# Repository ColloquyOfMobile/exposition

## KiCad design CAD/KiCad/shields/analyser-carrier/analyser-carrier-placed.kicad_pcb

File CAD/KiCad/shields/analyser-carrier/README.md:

# Direct-plug DFRobot analyser carrier

A second [continuous-wire schematic](wired/README.md) is available in `wired/`,
with an editable KiCad schematic and PDF. It preserves the original circuit,
uses no electrical net labels, and documents the drawing changes and the
purpose/necessity of existing test points and module modifications.

Five modified DFR0126 Audio Analyzer V2.0 modules plug directly into this
150 x 55mm carrier. Each site has one gold 1x6 female socket and one gold
1x2 female socket, both 2.54mm pitch. Downward male headers on the modules
mate with them; no module-to-carrier cables are used. The carrier's keyed
JA1 connector and two retention holes still match the backplane.

**Unmodified modules must not be plugged in.** The microphone feeds the
module's L input. The output is brought to the R-input header by the
following conversion. The user chose L for the microphone on 2026-10-19;
until then the conversion was the mirror image (R4 removed, L to OUT,
microphone on R). The white output connector can remain fitted but is unused.

The 2026-10-19 carrier revision follows this assignment at all five sites:
contact 1 = `microphone` (L), contact 4 = `analyser out` (converted R).
Schematic, copper, silkscreen, mechanical notes and fabrication packages
use the same mapping. Older carrier artwork requires the earlier module
conversion; do not mix revisions. Physical socket fit still needs checking.

## Convert each module

1. With power disconnected, remove **module R3, the 22K right-input summing
   resistor**. This is on the DFRobot module, not the carrier. If reference
   markings differ, identify the resistor between R and the input summing
   node from the schematic/continuity before removing it. Leave R4 (left
   input, the microphone's path) and the MSGEQ7 clock/reference parts in place.
2. Link the now-isolated **R signal terminal to OUT**, using a short insulated
   jumper on the module's component side. OUT is MSGEQ7 pin 3 and the signal
   contact of the white output connector. Do not connect it to +5V or GND.
   R3 must be removed first; otherwise this feeds output back into the input.
3. Refit the input connector positions as a downward-facing 1x6 male header
   (or two aligned 1x3 headers) and the control connector as a downward-facing
   1x2 male header. All eight mating pins point toward the carrier. Mark R as
   OUT permanently. The R input is no longer available for audio.
4. Before power, check continuity OUT-to-converted-R, continuity from L to
   R4, supply polarity at the mating pins, and isolation of converted R from
   the removed R3 summing-side pad. Check there is no solder bridge between
   +5V and ground. Confirm with the meter that the header pin reaching R4 sits
   at contact 1 and the one reaching R3 at contact 4: the L-then-R order of
   the two groups is photo-derived (below).
5. Seat the module fully in both sockets, then select nylon standoffs/shims
   matching that seated PCB gap. Do not force a predetermined spacer height
   against the sockets. M3 hardware retains the module; it does not pull the
   connectors into alignment. Module 0 is rotated 180 degrees.

DFRobot's V2 schematic identifies R4 as the left branch, R3 as the right,
and U1.3 as OUT:
https://dfimg.dfrobot.com/wiki/17648/DFR0126_msgeq7-spectrum-analyzer-module_schematics_V1.pdf
Both branches are 22K into one node, then C4 (0.01 uF) into MSGEQ7 IN, so
L and R are electrically interchangeable: the choice only decides which
header pin carries the microphone.

## Socket mapping

The table describes the carrier component-side view in each module's local
coordinate frame. The round mounting hole is (0,0); the slot is (20.32,0).
Module 0 rotates this complete pattern 180 degrees; the others do not.
Coordinates are **photo-derived assumptions**, not a manufacturer land pattern.

| Contact | Local X mm | Local Y mm | Signal / module marking |
|---|---:|---:|---|
| 1 | 3.81 | -5.08 | L microphone input |
| 2 | 6.35 | -5.08 | +5V (left group) |
| 3 | 8.89 | -5.08 | GND (left group) |
| 4 | 11.43 | -5.08 | OUT, formerly R |
| 5 | 13.97 | -5.08 | +5V (right group) |
| 6 | 16.51 | -5.08 | GND (right group) |
| 7 | 16.51 | 17.78 | R reset |
| 8 | 19.05 | 17.78 | S strobe |

All module +5V contacts use MEGA_5V; all module grounds use AGND. No digital
GND bond is added. The microphone signal feeds the L input. This table
matches the current schematic and copper.
ANA0-4, AGND and MEGA5V probe pads remain accessible. Leave the carrier out
when the Teensy adapter is fitted.

On 2026-10-08 the two-pin socket on each module position moved 1.27 mm
in local -X to match the corrected DFRobot J4. Reset now aligns in X with
input contact 6. Attached tracks and the nearby reset escape bends were
adjusted; native DRC reports zero violations and zero unconnected items.

## Photo-derived fit

The user authorized using the supplied photographs and standard pitch on
2026-10-07. The adopted grid has 2.54mm pin pitch and 22.86mm row separation.
Header offsets relative to holes, group ordering/orientation and the 20.32mm
hole spacing are inferred and require a physical fit/polarity check. The
29 x 32mm module envelope is also estimated. A 3.2mm hole and 5.74 x 3.2mm
slot allow mounting adjustment, but **slots do not correct socket misalignment**.

Print mounting-template.svg at 100%, verify its 50mm scale, then compare all
eight module pins and both mounting holes. Confirm against one converted
module before manufacturing the set. This is an engineering prototype, not
a fit-verified fabrication release. Native DRC does not prove connector fit.
mechanical.json preserves these assumptions; socket-assembly.csv lists hardware.

M1-M5 in the KiCad BOM are composite module/socket assemblies. Fit the purchased
modules after soldering sockets to the carrier; do not solder the modules to it.
Use carrier.py to regenerate, then route.py, finish.py, planes.py, check.py and
verify.py. The latter independently checks all eight mating pad positions/nets.

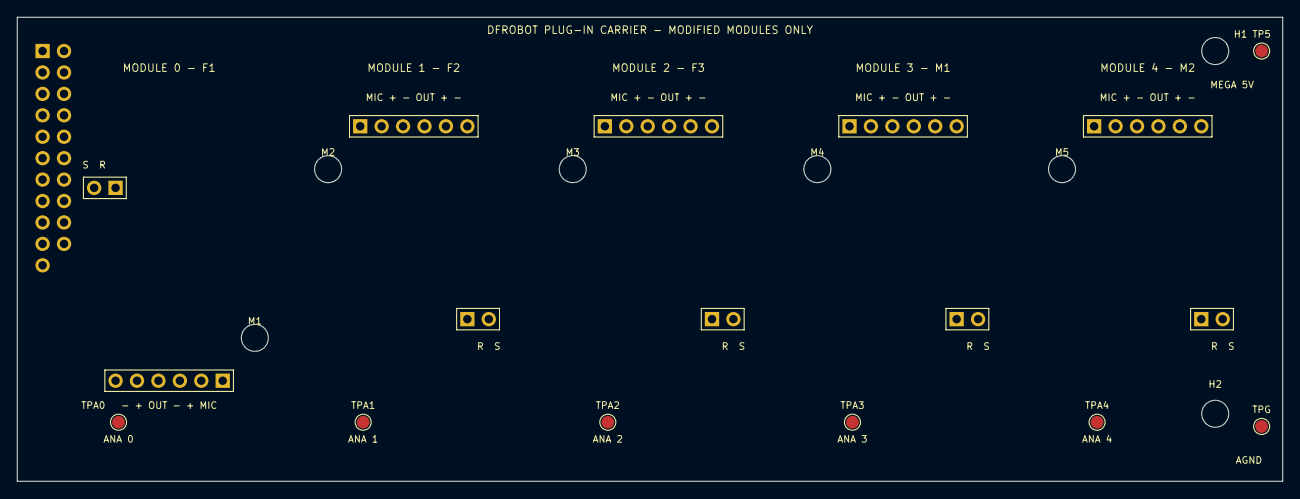
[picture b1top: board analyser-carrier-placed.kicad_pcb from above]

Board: 2 copper layers, 150.0 x 55.0 mm, 15 parts (1 on the bottom side), 14 nets, no tracks yet.

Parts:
H1, H2: M3 carrier retention; MountingHole_3.2mm_M3
JA1: ANALYSER - KEY 22; Socket_2x11_Key22_PlugCarrier
M1, M2, M3, M4, M5: DFR0126 MODIFIED / PLUG-IN; DFR0126_PlugIn_Photo
TP5: MEGA_5V; TestPoint_Pad_D1.5mm
TPA0: female1/analyser out; TestPoint_Pad_D1.5mm
TPA1: female2/analyser out; TestPoint_Pad_D1.5mm
TPA2: female3/analyser out; TestPoint_Pad_D1.5mm
TPA3: male1/analyser out; TestPoint_Pad_D1.5mm
TPA4: male2/analyser out; TestPoint_Pad_D1.5mm
TPG: AGND; TestPoint_Pad_D1.5mm

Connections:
AGND: JA1.2, JA1.4, JA1.6, JA1.8, JA1.10, JA1.16, M1.3, M1.6, M2.3, M2.6, M3.3, M3.6, M4.3, M4.6, M5.3, M5.6, TPG.1
MEGA_5V: JA1.19, M1.2, M1.5, M2.2, M2.5, M3.2, M3.5, M4.2, M4.5, M5.2, M5.5, TP5.1
analyser/reset: JA1.18, M1.7, M2.7, M3.7, M4.7, M5.7
analyser/strobe: JA1.17, M1.8, M2.8, M3.8, M4.8, M5.8
female1/analyser out: JA1.11, M1.4, TPA0.1
female1/microphone: JA1.1, M1.1
female2/analyser out: JA1.12, M2.4, TPA1.1
female2/microphone: JA1.3, M2.1
female3/analyser out: JA1.13, M3.4, TPA2.1
female3/microphone: JA1.5, M3.1
male1/analyser out: JA1.14, M4.4, TPA3.1
male1/microphone: JA1.7, M4.1
male2/analyser out: JA1.15, M5.4, TPA4.1
male2/microphone: JA1.9, M5.1

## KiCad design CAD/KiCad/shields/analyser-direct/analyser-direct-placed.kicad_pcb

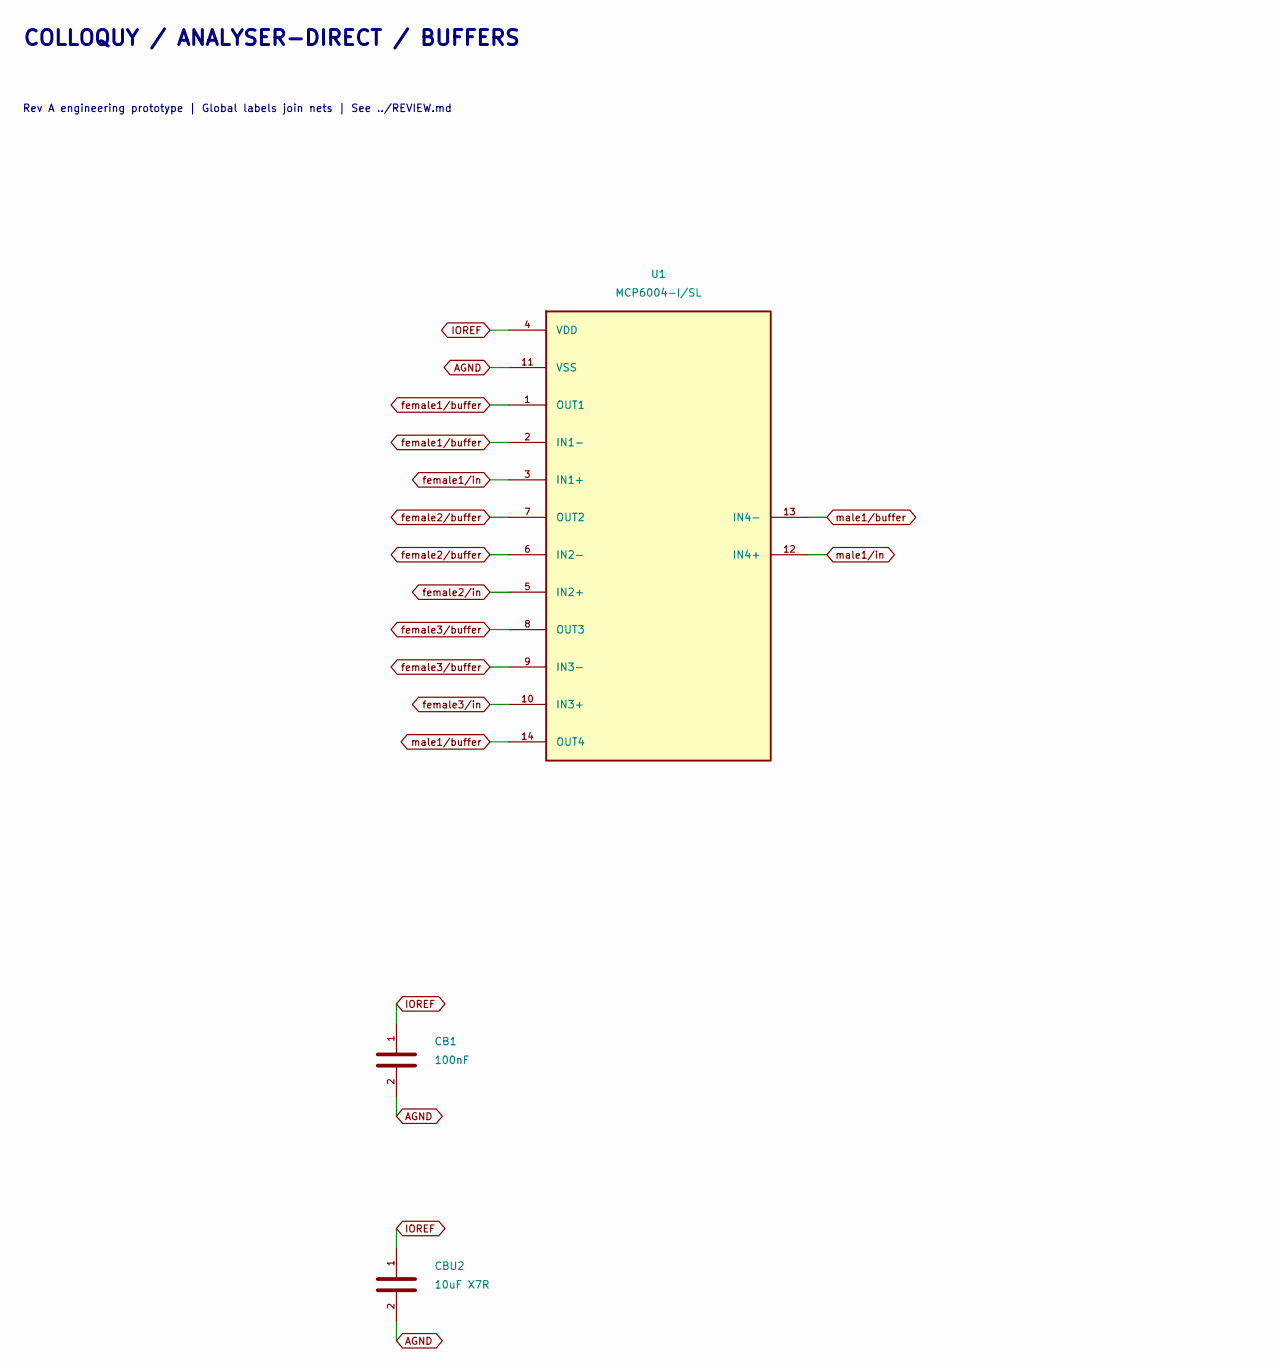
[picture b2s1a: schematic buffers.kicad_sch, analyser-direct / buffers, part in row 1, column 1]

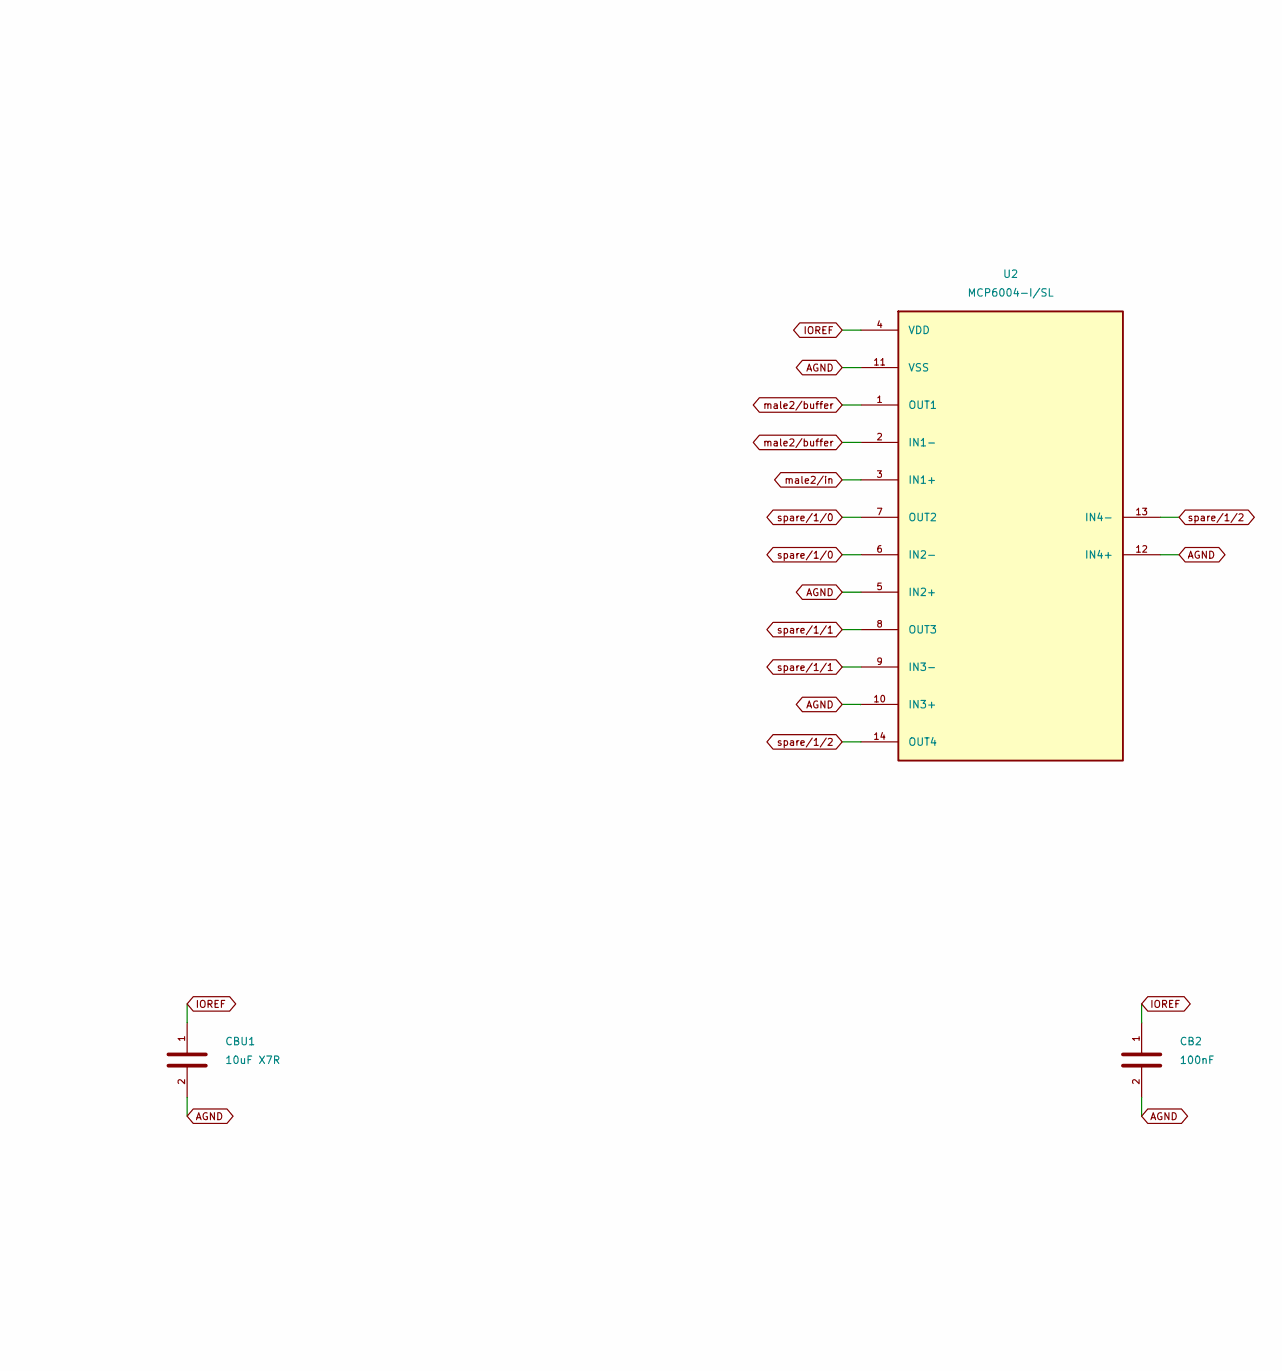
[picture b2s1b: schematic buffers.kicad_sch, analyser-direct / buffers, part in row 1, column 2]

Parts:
CB1, CB2: 100nF; C_0603_1608Metric
CBU1, CBU2: 10uF X7R; C_0805_2012Metric
U1, U2: MCP6004-I/SL; SOIC-14_3.9x8.7mm_P1.27mm

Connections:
AGND: CB1.2, CB2.2, CBU1.2, CBU2.2, U1.11 (VSS), U2.5 (IN2+), U2.10 (IN3+), U2.11 (VSS), U2.12 (IN4+); also elsewhere on the board
IOREF: CB1.1, CB2.1, CBU1.1, CBU2.1, U1.4 (VDD), U2.4 (VDD); also elsewhere on the board
female1/buffer: U1.1 (OUT1), U1.2 (IN1-); also elsewhere on the board
female1/in: U1.3 (IN1+); also elsewhere on the board
female2/buffer: U1.6 (IN2-), U1.7 (OUT2); also elsewhere on the board
female2/in: U1.5 (IN2+); also elsewhere on the board
female3/buffer: U1.8 (OUT3), U1.9 (IN3-); also elsewhere on the board
female3/in: U1.10 (IN3+); also elsewhere on the board
male1/buffer: U1.13 (IN4-), U1.14 (OUT4); also elsewhere on the board
male1/in: U1.12 (IN4+); also elsewhere on the board
male2/buffer: U2.1 (OUT1), U2.2 (IN1-); also elsewhere on the board
male2/in: U2.3 (IN1+); also elsewhere on the board
spare/1/0: U2.6 (IN2-), U2.7 (OUT2)
spare/1/1: U2.8 (OUT3), U2.9 (IN3-)
spare/1/2: U2.13 (IN4-), U2.14 (OUT4)

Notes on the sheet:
COLLOQUY / ANALYSER-DIRECT / BUFFERS
Rev A engineering prototype | Global labels join nets | See ../REVIEW.md

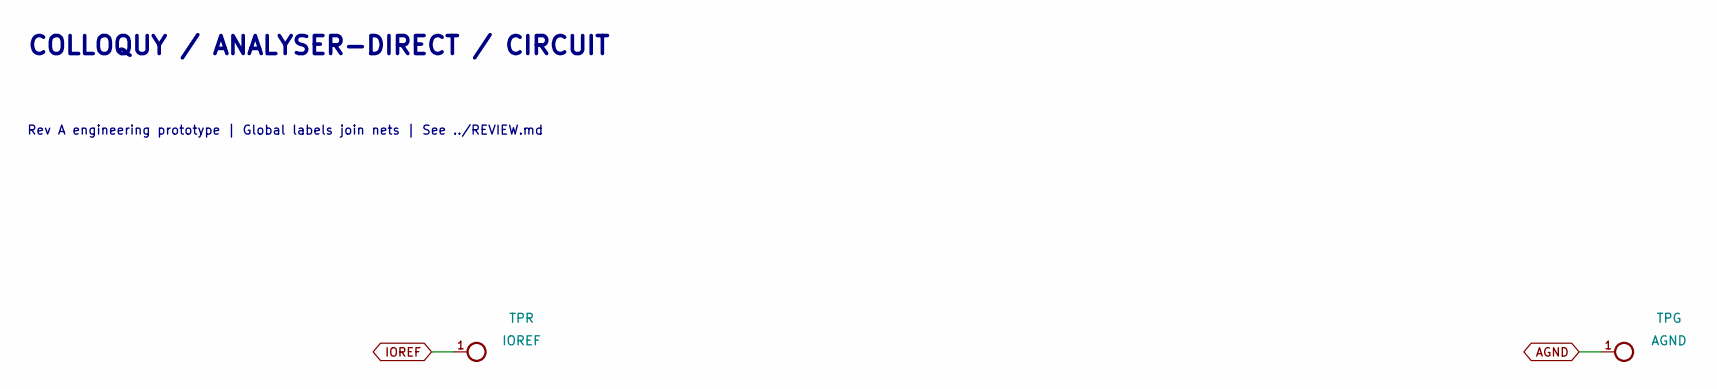
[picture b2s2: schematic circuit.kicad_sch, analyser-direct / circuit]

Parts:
TPG: AGND; TestPoint_Pad_D1.5mm
TPR: IOREF; TestPoint_Pad_D1.5mm

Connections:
AGND: TPG.1; also elsewhere on the board
IOREF: TPR.1; also elsewhere on the board

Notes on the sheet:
COLLOQUY / ANALYSER-DIRECT / CIRCUIT
Rev A engineering prototype | Global labels join nets | See ../REVIEW.md

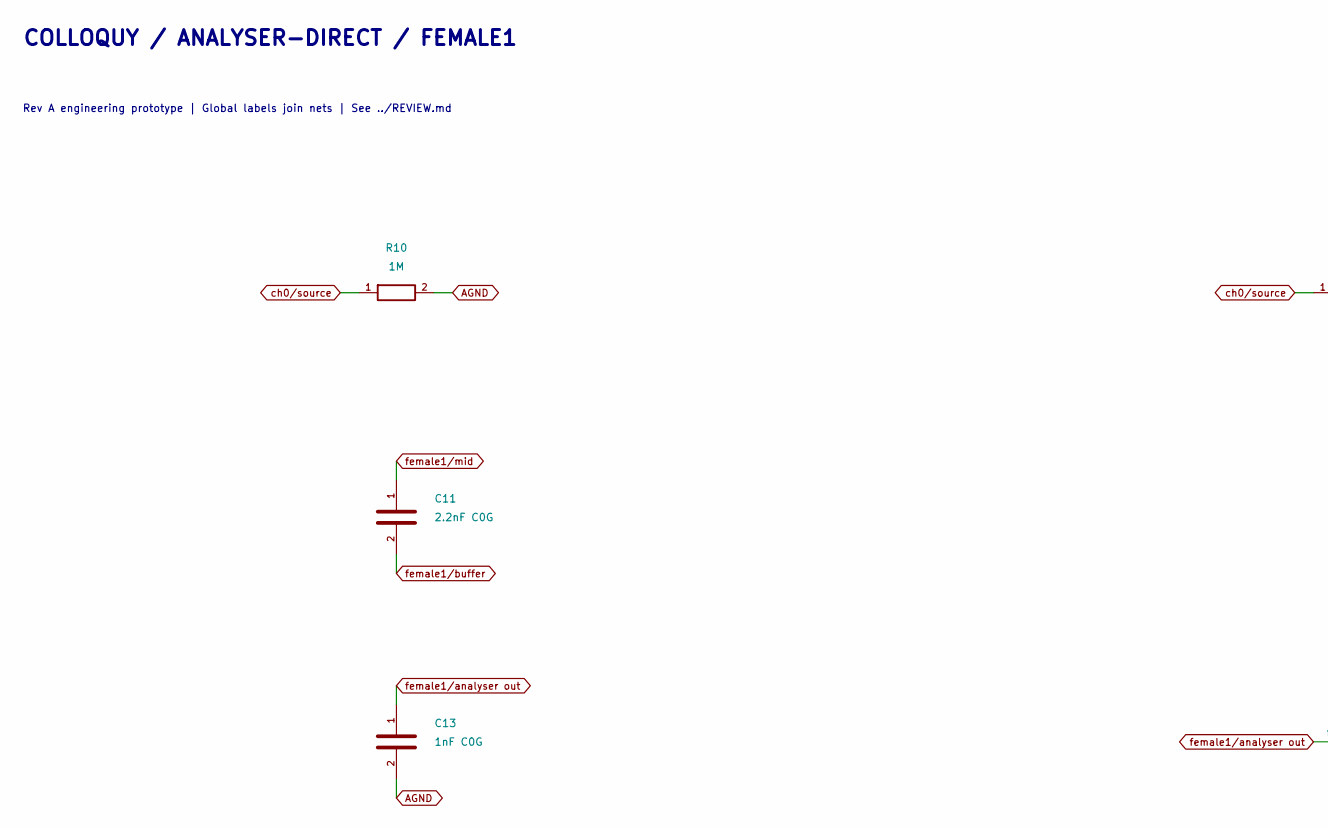
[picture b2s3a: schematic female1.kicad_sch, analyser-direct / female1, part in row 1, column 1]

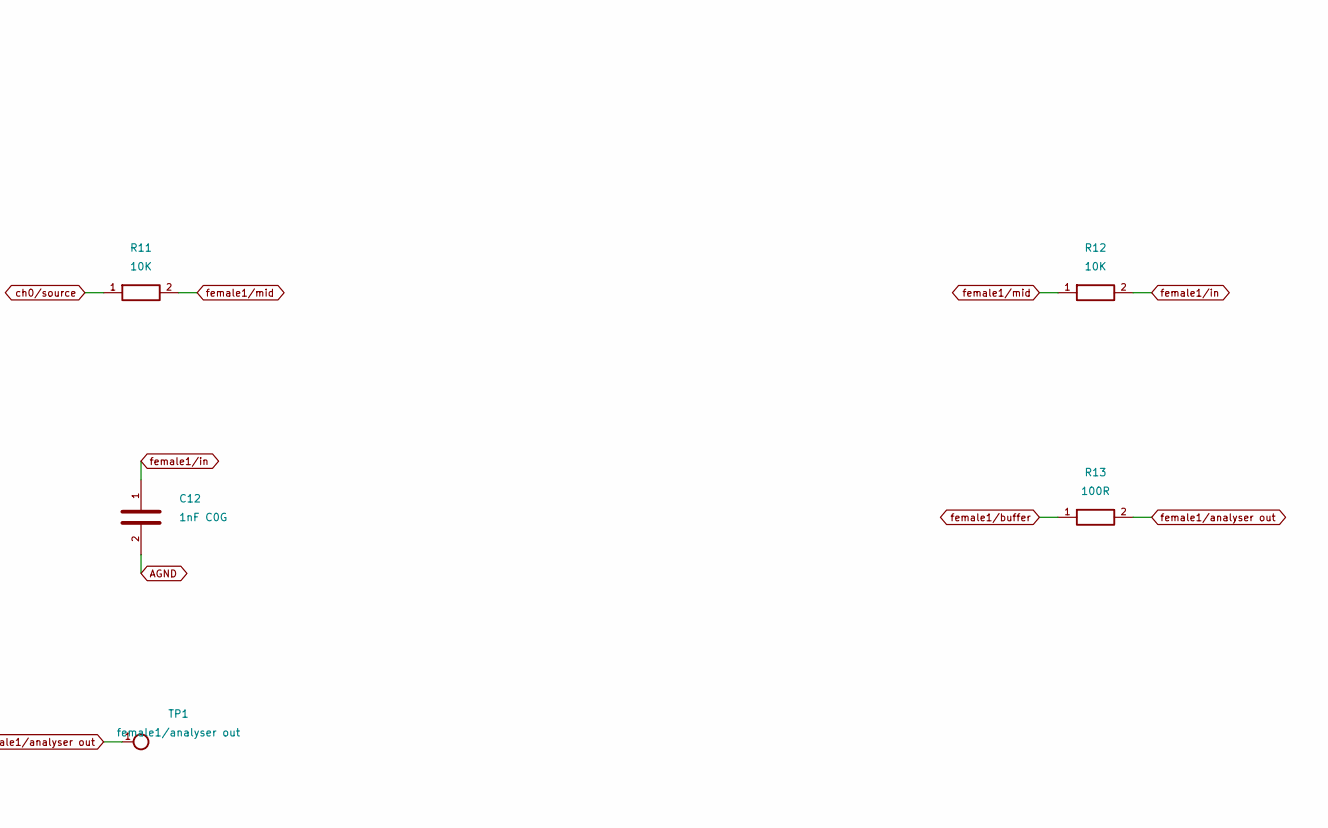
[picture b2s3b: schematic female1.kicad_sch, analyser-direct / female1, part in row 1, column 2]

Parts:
C11: 2.2nF C0G; C_0603_1608Metric
C12, C13: 1nF C0G; C_0603_1608Metric
R10: 1M; R_0603_1608Metric
R11, R12: 10K; R_0603_1608Metric
R13: 100R; R_0603_1608Metric
TP1: female1/analyser out; TestPoint_Pad_D1.5mm

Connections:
AGND: C12.2, C13.2, R10.2; also elsewhere on the board
ch0/source: R10.1, R11.1; also elsewhere on the board
female1/analyser out: C13.1, R13.2, TP1.1; also elsewhere on the board
female1/buffer: C11.2, R13.1; also elsewhere on the board
female1/in: C12.1, R12.2; also elsewhere on the board
female1/mid: C11.1, R11.2, R12.1

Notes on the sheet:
COLLOQUY / ANALYSER-DIRECT / FEMALE1
Rev A engineering prototype | Global labels join nets | See ../REVIEW.md

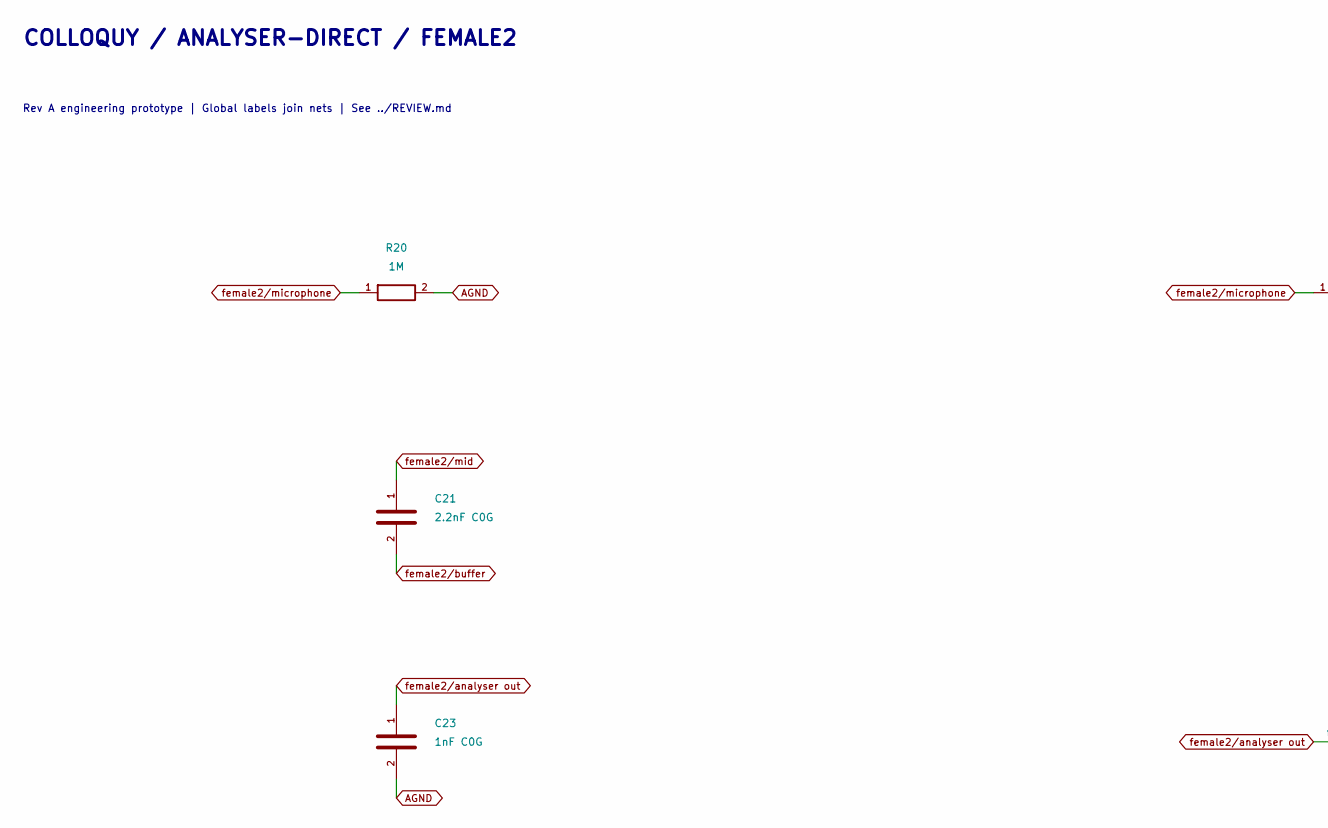
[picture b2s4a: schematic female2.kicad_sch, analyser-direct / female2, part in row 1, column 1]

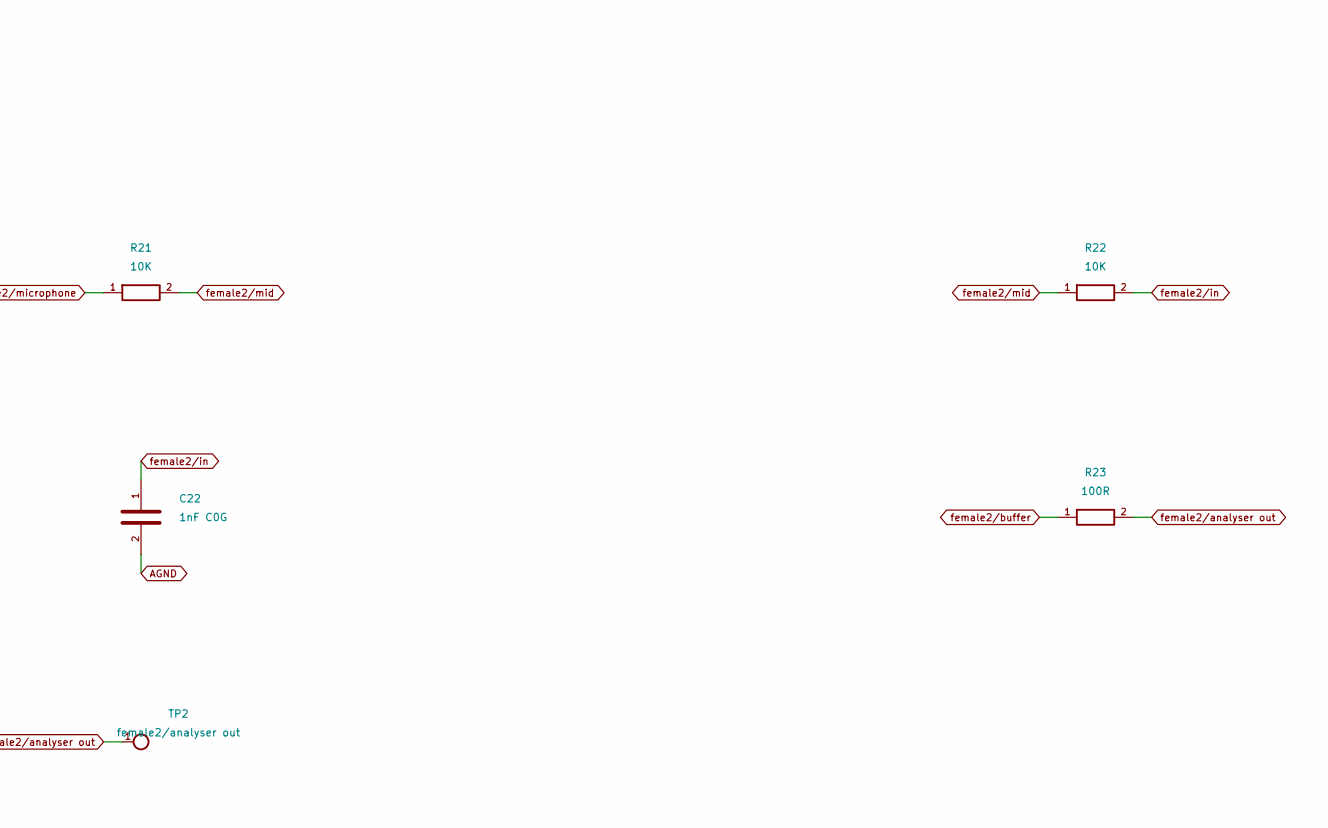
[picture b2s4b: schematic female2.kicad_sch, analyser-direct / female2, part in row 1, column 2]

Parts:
C21: 2.2nF C0G; C_0603_1608Metric
C22, C23: 1nF C0G; C_0603_1608Metric
R20: 1M; R_0603_1608Metric
R21, R22: 10K; R_0603_1608Metric
R23: 100R; R_0603_1608Metric
TP2: female2/analyser out; TestPoint_Pad_D1.5mm

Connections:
AGND: C22.2, C23.2, R20.2; also elsewhere on the board
female2/analyser out: C23.1, R23.2, TP2.1; also elsewhere on the board
female2/buffer: C21.2, R23.1; also elsewhere on the board
female2/in: C22.1, R22.2; also elsewhere on the board
female2/microphone: R20.1, R21.1; also elsewhere on the board
female2/mid: C21.1, R21.2, R22.1

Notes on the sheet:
COLLOQUY / ANALYSER-DIRECT / FEMALE2
Rev A engineering prototype | Global labels join nets | See ../REVIEW.md

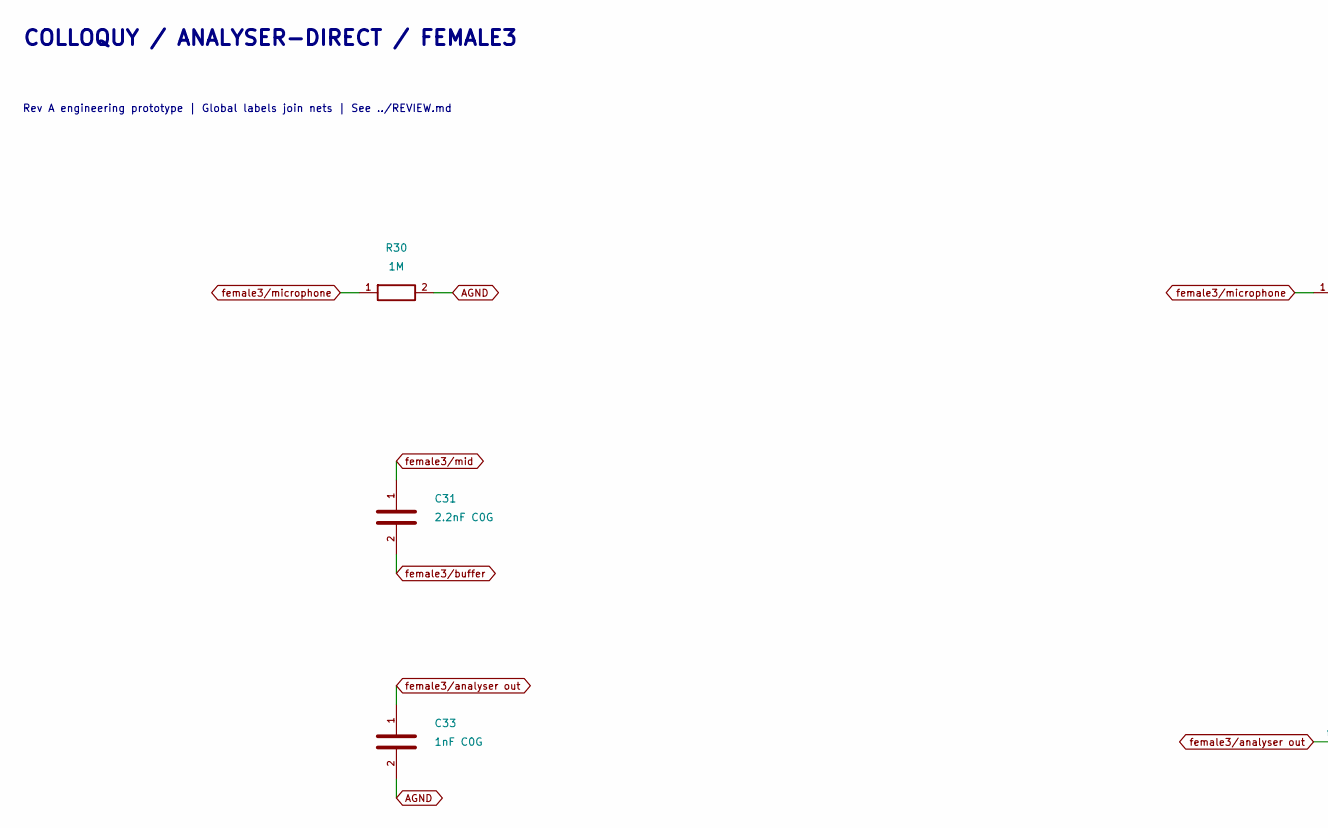
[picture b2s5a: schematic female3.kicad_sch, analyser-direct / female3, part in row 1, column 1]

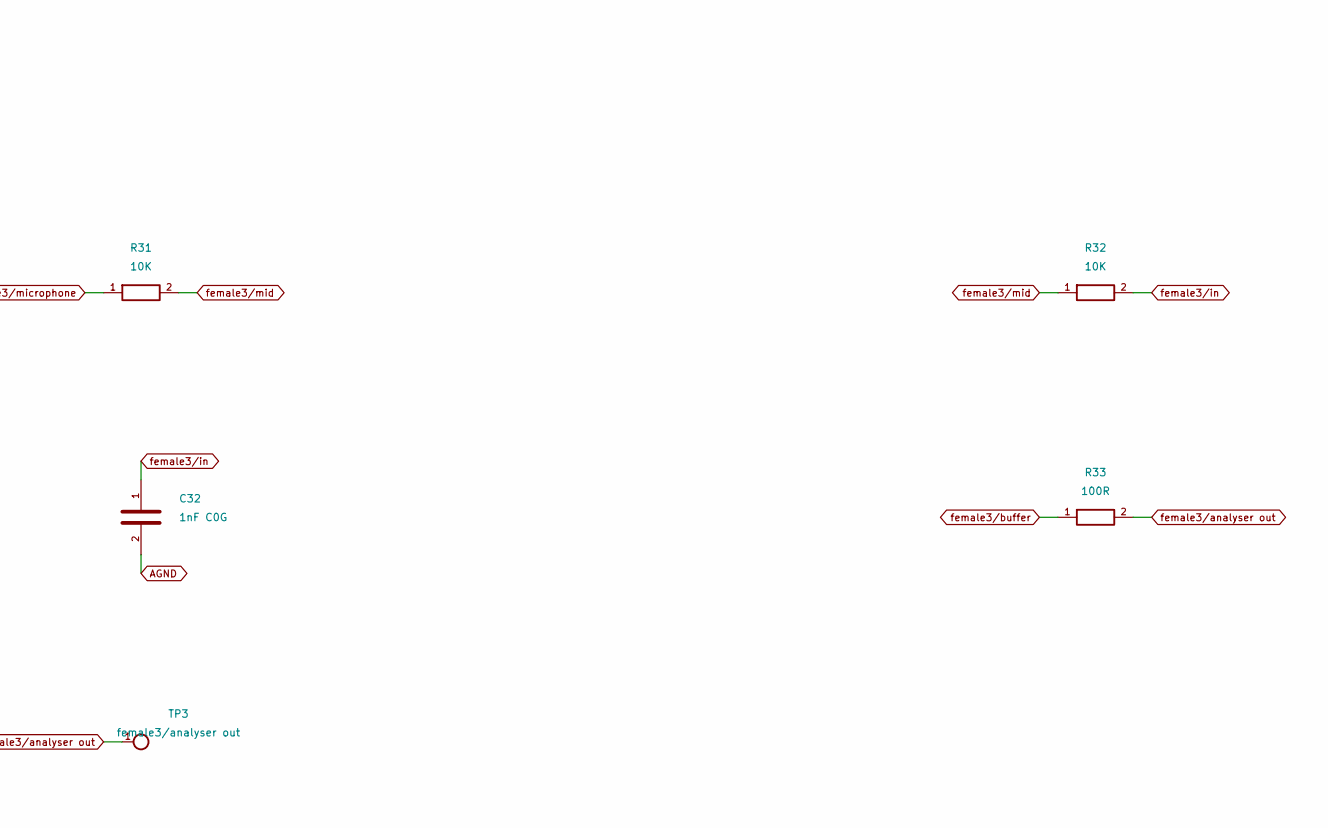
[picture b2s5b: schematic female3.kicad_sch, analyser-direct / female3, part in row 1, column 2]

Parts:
C31: 2.2nF C0G; C_0603_1608Metric
C32, C33: 1nF C0G; C_0603_1608Metric
R30: 1M; R_0603_1608Metric
R31, R32: 10K; R_0603_1608Metric
R33: 100R; R_0603_1608Metric
TP3: female3/analyser out; TestPoint_Pad_D1.5mm

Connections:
AGND: C32.2, C33.2, R30.2; also elsewhere on the board
female3/analyser out: C33.1, R33.2, TP3.1; also elsewhere on the board
female3/buffer: C31.2, R33.1; also elsewhere on the board
female3/in: C32.1, R32.2; also elsewhere on the board
female3/microphone: R30.1, R31.1; also elsewhere on the board
female3/mid: C31.1, R31.2, R32.1

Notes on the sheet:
COLLOQUY / ANALYSER-DIRECT / FEMALE3
Rev A engineering prototype | Global labels join nets | See ../REVIEW.md

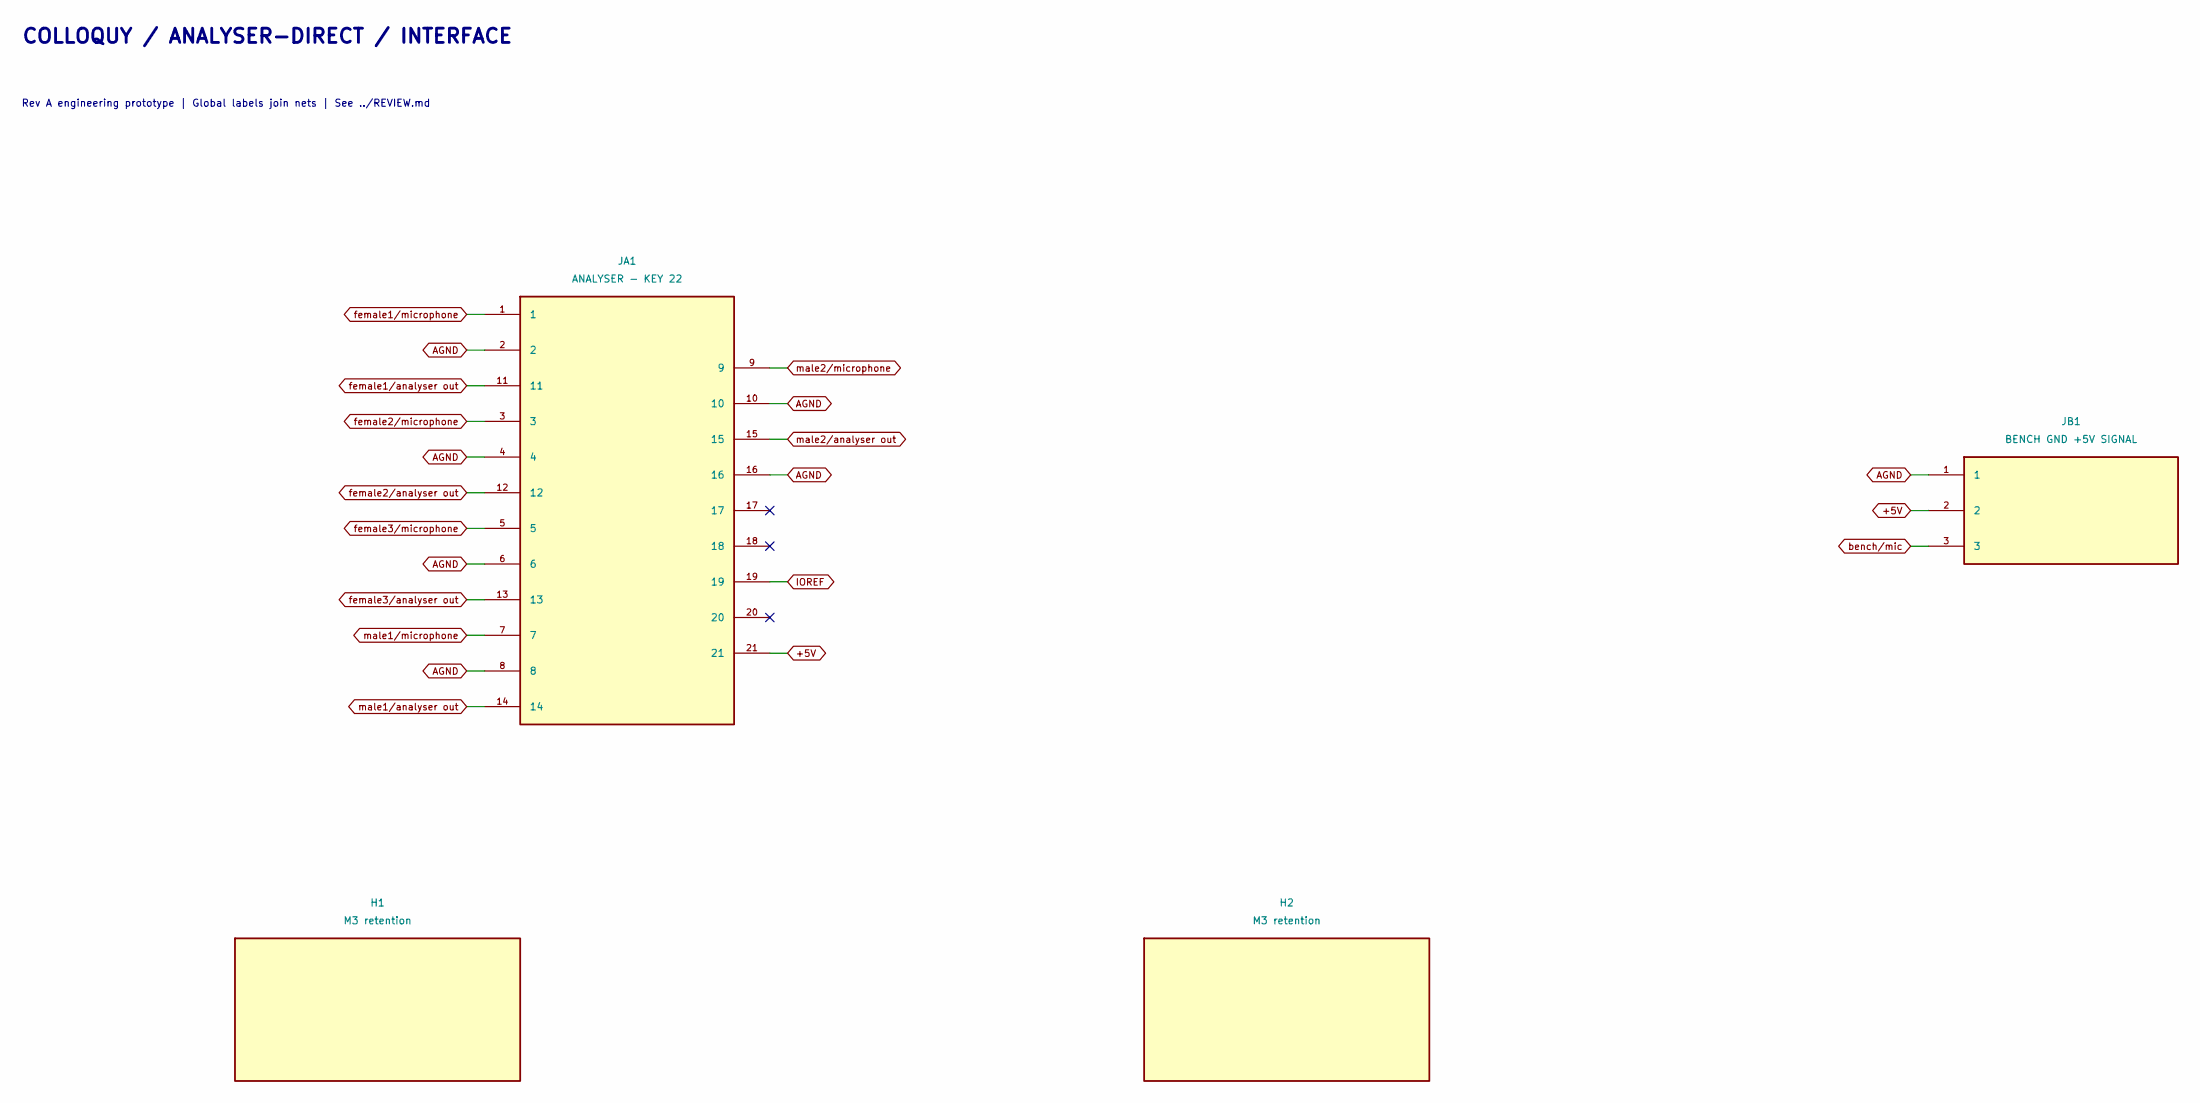
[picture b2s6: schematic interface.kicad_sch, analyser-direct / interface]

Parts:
H1, H2: M3 retention; MountingHole_3.2mm_M3
JA1: ANALYSER - KEY 22; Socket_2x11_Key22
JB1: BENCH GND +5V SIGNAL; JST_EH_B3B-EH-A_1x03_P2.50mm_Vertical

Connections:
+5V: JA1.21, JB1.2
AGND: JA1.2, JA1.4, JA1.6, JA1.8, JA1.10, JA1.16, JB1.1; also elsewhere on the board
IOREF: JA1.19; also elsewhere on the board
bench/mic: JB1.3; also elsewhere on the board
female1/analyser out: JA1.11; also elsewhere on the board
female1/microphone: JA1.1; also elsewhere on the board
female2/analyser out: JA1.12; also elsewhere on the board
female2/microphone: JA1.3; also elsewhere on the board
female3/analyser out: JA1.13; also elsewhere on the board
female3/microphone: JA1.5; also elsewhere on the board
male1/analyser out: JA1.14; also elsewhere on the board
male1/microphone: JA1.7; also elsewhere on the board
male2/analyser out: JA1.15; also elsewhere on the board
male2/microphone: JA1.9; also elsewhere on the board

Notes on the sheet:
COLLOQUY / ANALYSER-DIRECT / INTERFACE
Rev A engineering prototype | Global labels join nets | See ../REVIEW.md

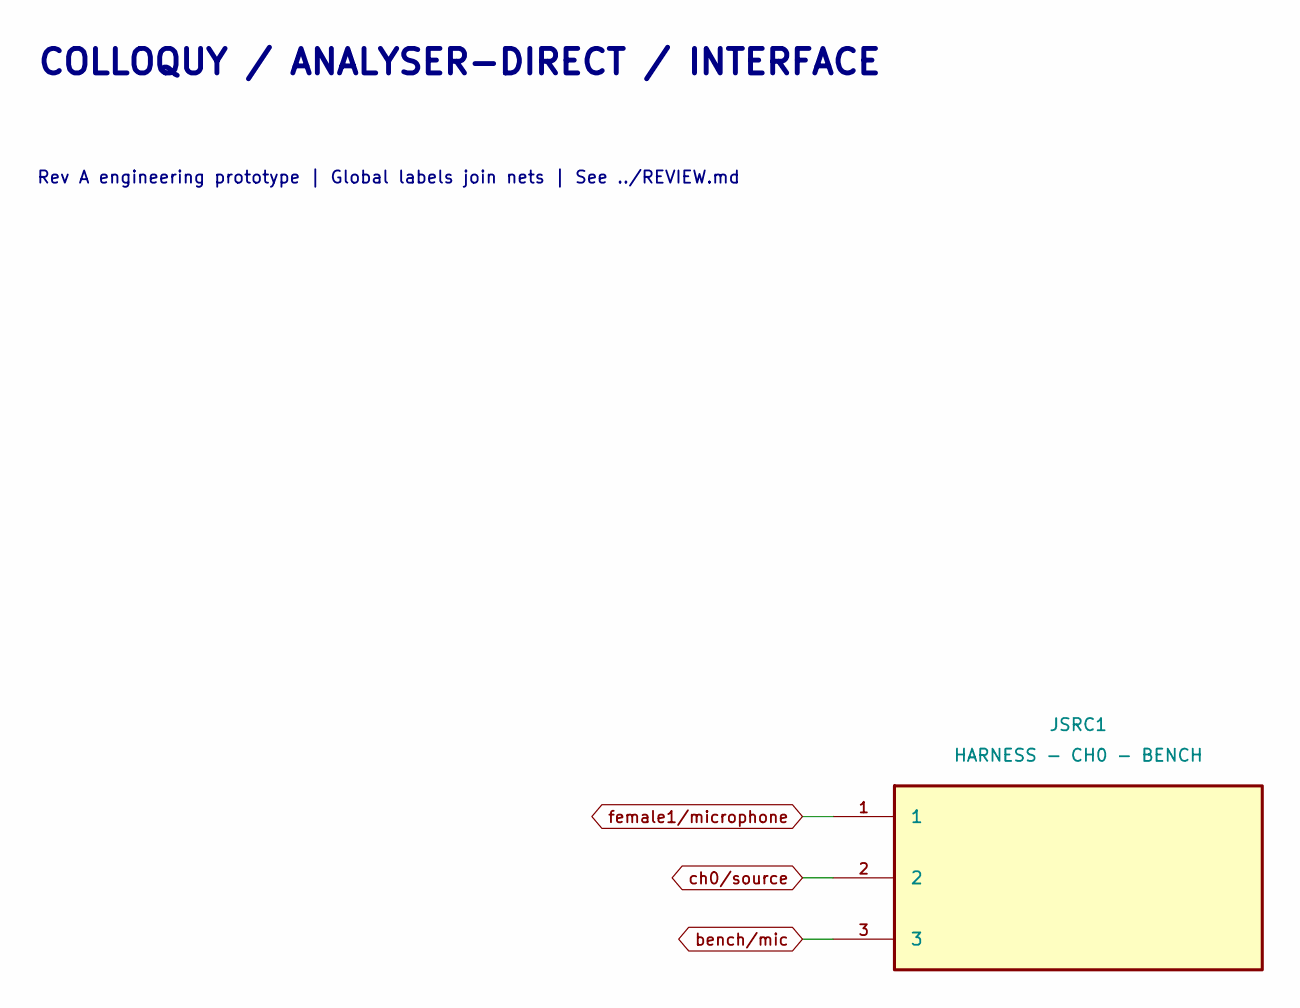
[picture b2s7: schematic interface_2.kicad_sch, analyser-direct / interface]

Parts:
JSRC1: HARNESS - CH0 - BENCH; PinHeader_1x03_P2.54mm_Vertical

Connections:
bench/mic: JSRC1.3; also elsewhere on the board
ch0/source: JSRC1.2; also elsewhere on the board
female1/microphone: JSRC1.1; also elsewhere on the board

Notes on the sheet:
COLLOQUY / ANALYSER-DIRECT / INTERFACE
Rev A engineering prototype | Global labels join nets | See ../REVIEW.md
